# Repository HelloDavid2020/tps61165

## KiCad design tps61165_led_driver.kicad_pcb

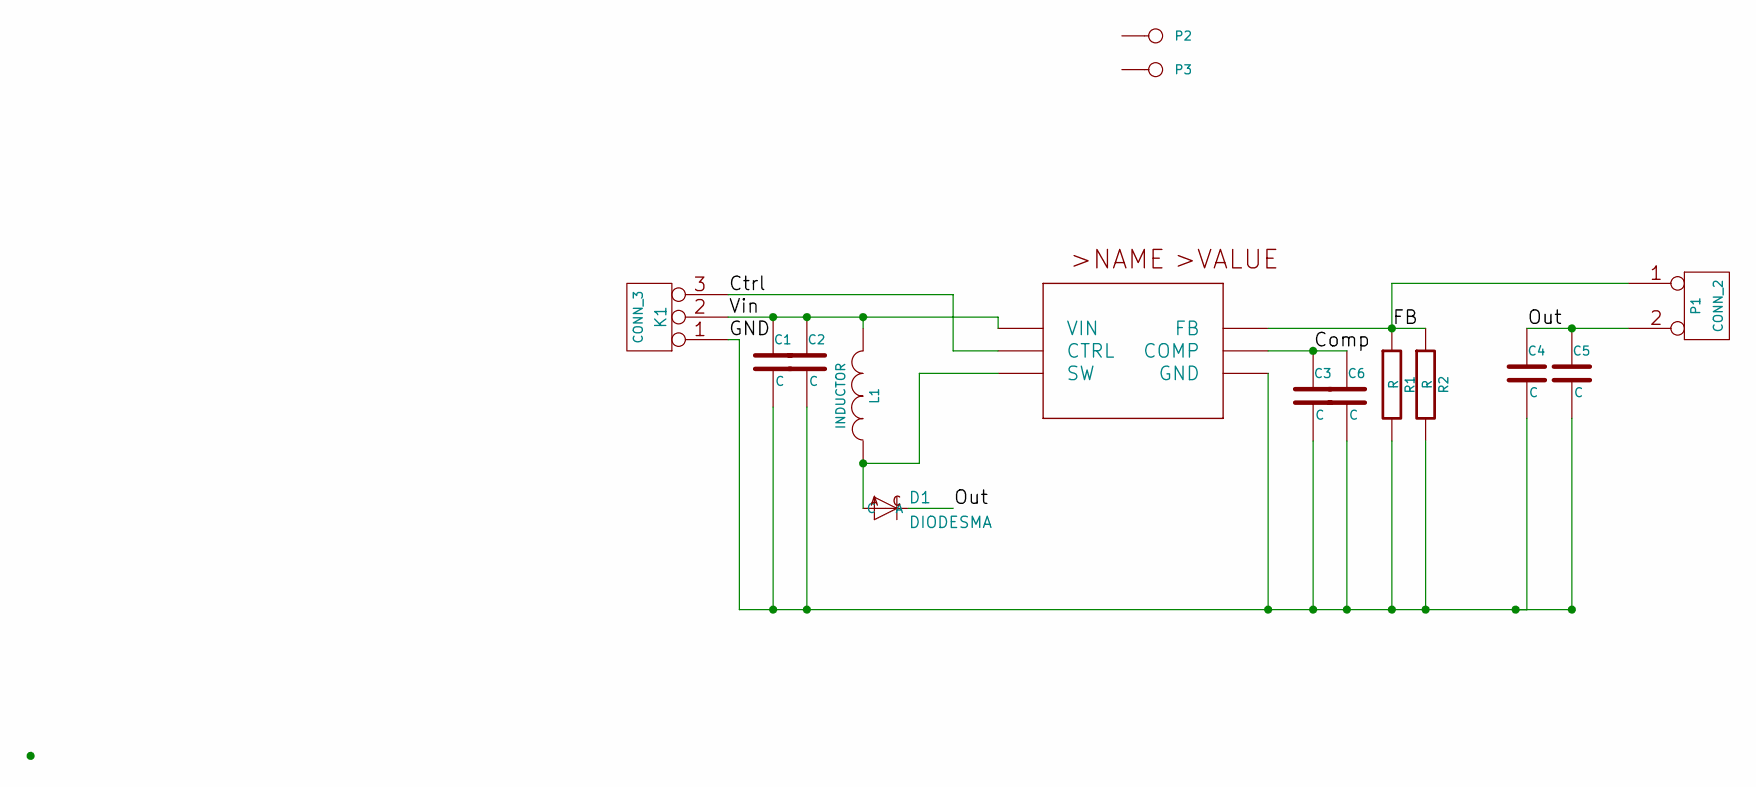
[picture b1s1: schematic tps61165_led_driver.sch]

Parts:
C1, C2, C3, C4, C5, C6: C
D1: DIODESMA; SparkFun-SMA-DIODE
K1: CONN_3
L1: INDUCTOR
P1: CONN_2
P2, P3: CONN_1
R1, R2: R
U1: TPS61165_DBV_6_DBV6

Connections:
/Comp: C3.1, C6.1, U1.5 (COMP)
/Ctrl: K1.3, U1.2 (CTRL)
/FB: P1.1, R1.1, R2.1, U1.6 (FB)
/GND: C1.2, C2.2, C3.2, C4.2, C5.2, C6.2, K1.1, R1.2, R2.2, U1.4 (GND)
/Out: C4.1, C5.1, D1.C, P1.2 (PM)
/Vin: C1.1, C2.1, K1.2 (PM), L1.2, U1.1 (VIN)
unnamed: D1.A, L1.1, U1.3 (SW)

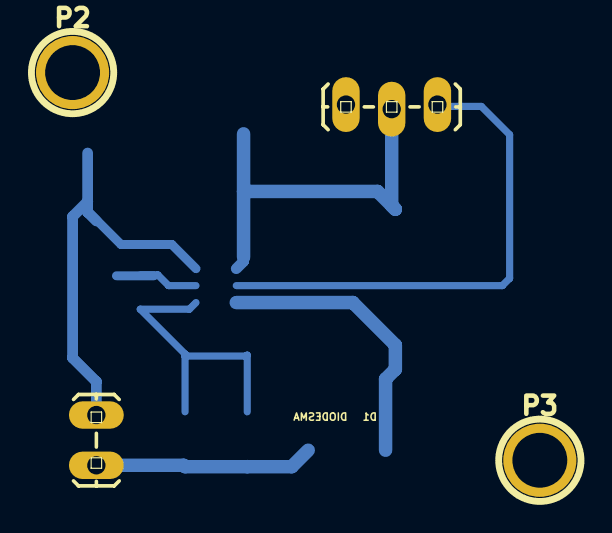
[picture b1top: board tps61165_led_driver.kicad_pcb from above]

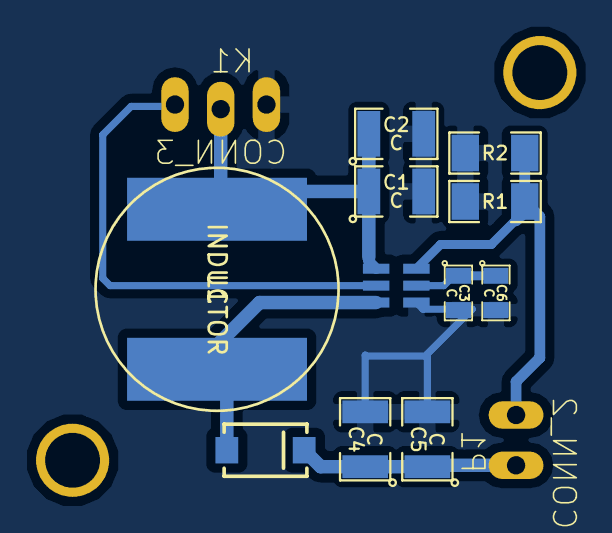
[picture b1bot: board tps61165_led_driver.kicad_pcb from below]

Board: 2 copper layers, 15 parts (11 on the bottom side), 7 nets.

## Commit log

2015-03-22 ADD: first commit
2015-03-23 ADD: pdf
2015-03-23 ADD: pdf, added cap
